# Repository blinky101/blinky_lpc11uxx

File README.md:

# LPC11uxx Example Project: Blinky

Simple Hello World-like blinky programs for the LPC11uxx platform.
This repositories contains three blinky programs, in increasing order of complexity / abstraction level:

1. [bare-metal](/bare-metal/): A blinky program in one file, with no dependencies at all
2. [basic](/basic/): Some of the low-level stuff is in separate functions, but still a very simple c program
3. [cpm](/cpm/): Using CPM as c package manager: reuseable dependencies are in separate repositories

See [the blinky website](https://blinky101.github.io/blinky_lpc11uxx/) and the per-project *README* files for more information.

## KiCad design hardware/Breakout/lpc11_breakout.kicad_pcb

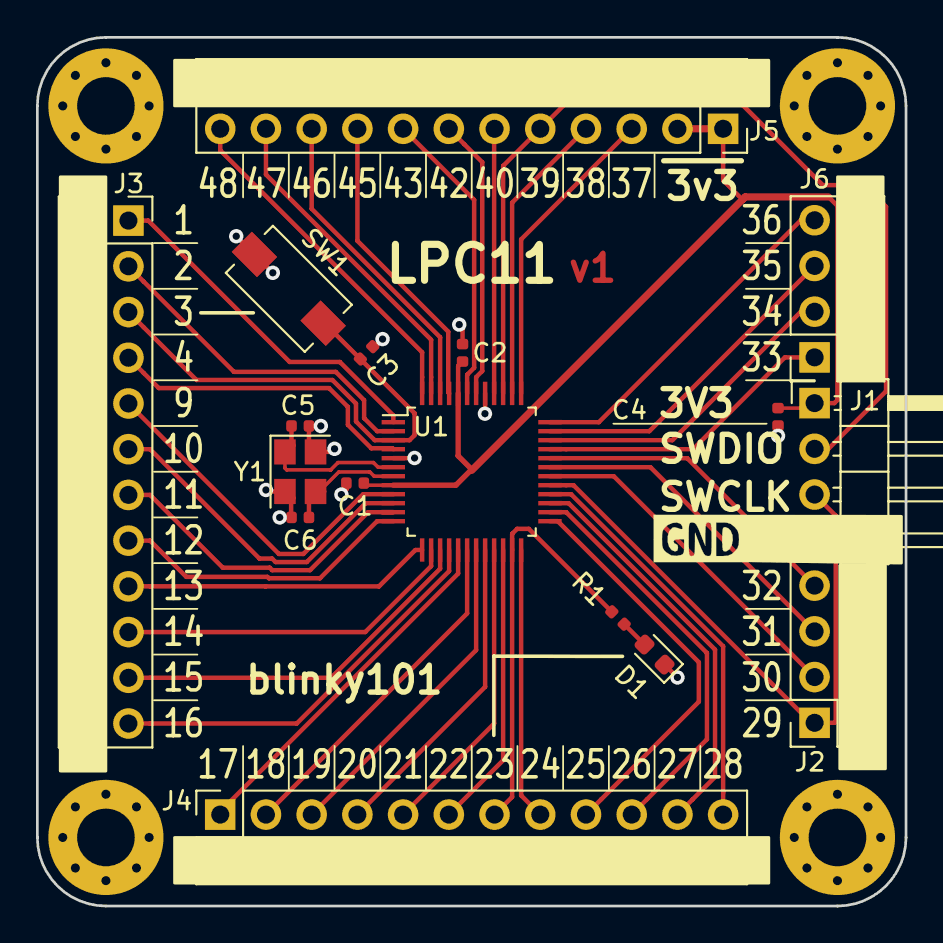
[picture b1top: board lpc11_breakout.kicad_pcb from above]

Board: 2 copper layers, 48.3 x 48.3 mm, 21 parts (0 on the bottom side), 47 nets.

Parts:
C1, C2, C4: 100nF; C_0402_1005Metric
C3, C5, C6: 18pF; C_0402_1005Metric
D1: LED; LED_0603_1608Metric
H1, H2, H3, H4: MountingHole_Pad; MountingHole_3.2mm_M3_Pad_Via
J1: Conn_01x04_Male; PinHeader_1x04_P2.54mm_Horizontal
J2, J6: Conn_02x04_Odd_Even; PinSocket_2x04_P2.54mm_Vertical
J3, J4, J5: Conn_02x12_Odd_Even; PinSocket_2x12_P2.54mm_Vertical
R1: 270R; R_0402_1005Metric
SW1: SW_Push; SW_SPST_EVQPE1
U1: LPC1115JBD48-303; LQFP-48_7x7mm_P0.5mm
Y1: MCSJK-7U-12.00-10-10-80-B-10; Crystal_SMD_3225-4Pin_3.2x2.5mm

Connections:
+3V3: C1.1, C2.1, C4.1, J1.1, J5.1, J5.3, U1.8, U1.44
/1: J3.1, U1.1
/2: J3.3, U1.2
/3: C3.1, J3.5, SW1.1, U1.3
/4: J3.7, U1.4
/9: J3.9, U1.9
/10: J3.11, U1.10
/11: J3.13, U1.11
/12: J3.15, U1.12
/13: J3.17, U1.13
/14: J3.19, U1.14
/15: J3.21, U1.15
/16: J3.23, U1.16
/17: J4.1, U1.17
/18: J4.3, U1.18
/19: J4.5, U1.19
/20: J4.7, U1.20
/21: J4.9, U1.21
/22: J4.11, U1.22
/23: J4.13, R1.1, U1.23
/24: J4.15, U1.24
/25: J4.17, U1.25
/26: J4.19, U1.26
/27: J4.21, U1.27
/28: J4.23, U1.28
/30: J2.3, U1.30
/31: J2.5, U1.31
/32: J2.7, U1.32
/33: J6.1, U1.33
/34: J6.3, U1.34
/35: J6.5, U1.35
/36: J6.7, U1.36
/37: J5.5, U1.37
/38: J5.7, U1.38
/40: J5.11, U1.40
/42: J5.13, U1.42
/43: J5.15, U1.43
/45: J5.17, U1.45
/46: J5.19, U1.46
/47: J5.21, U1.47
/48: J5.23, U1.48
/SWCLK_29: J1.3, J2.1, U1.29
/SWDIO_39: J1.2, J5.9, U1.39
GND: C1.2, C2.2, C3.2, C4.2, C5.2, C6.2, D1.1, J1.4, J2.2, J2.4, J2.6, J2.8, J3.2, J3.4, J3.6, J3.8, J3.10, J3.12, J3.14, J3.16, J3.18, J3.20, J3.22, J3.24, J4.2, J4.4, J4.6, J4.8, J4.10, J4.12, J4.14, J4.16, J4.18, J4.20, J4.22, J4.24, J5.2, J5.4, J5.6, J5.8, J5.10, J5.12, J5.14, J5.16, J5.18, J5.20, J5.22, J5.24, J6.2, J6.4, J6.6, J6.8, SW1.2, U1.5, U1.41, Y1.2, Y1.4
unnamed: C5.1, U1.6, Y1.1
unnamed: C6.1, U1.7, Y1.3
unnamed: D1.2, R1.2

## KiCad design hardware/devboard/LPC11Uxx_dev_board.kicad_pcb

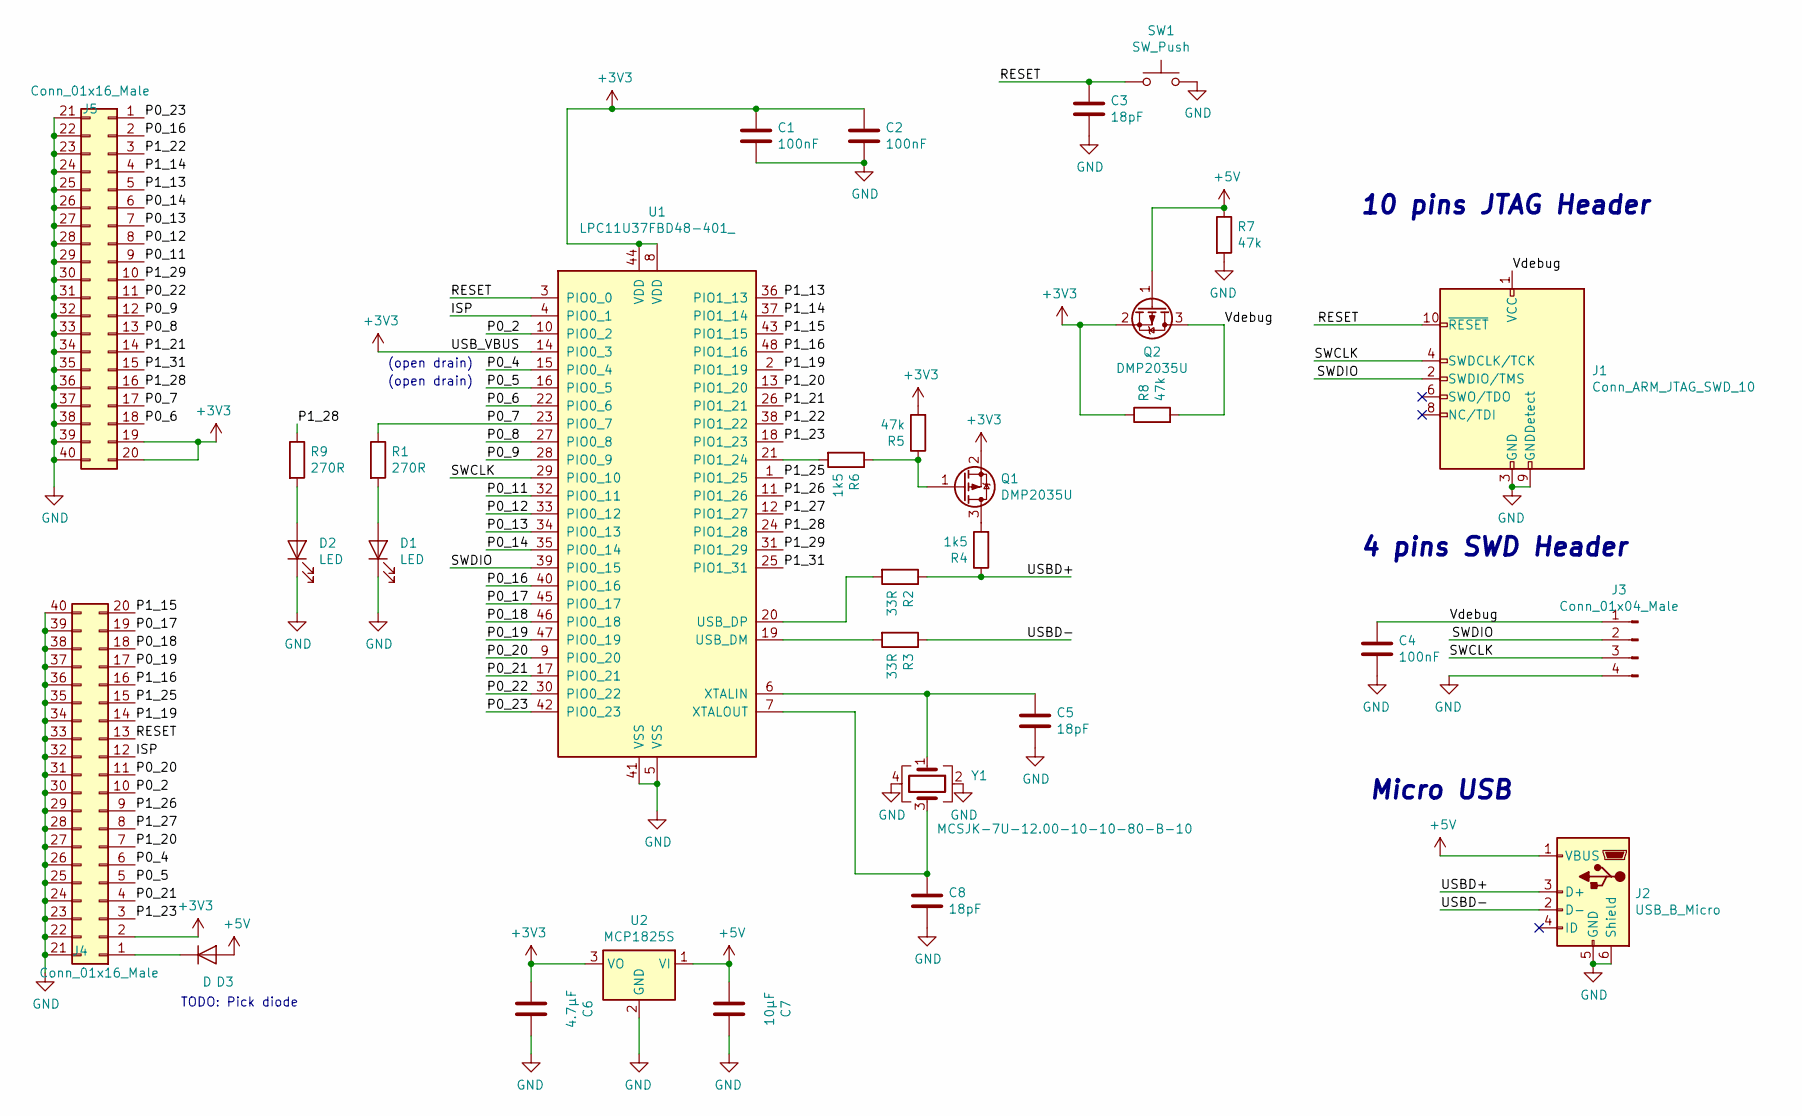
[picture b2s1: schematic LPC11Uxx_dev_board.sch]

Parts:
C1, C2, C4: 100nF; C_0402_1005Metric
C3, C5, C8: 18pF; C_0402_1005Metric
C6: 4.7µF; C_0805_2012Metric
C7: 10µF; C_0805_2012Metric
D1, D2: LED; LED_0603_1608Metric
D3: D; D_SOD-123F
J1: Conn_ARM_JTAG_SWD_10; PinHeader_2x05_P1.27mm_Vertical_SMD
J2: USB_B_Micro; USB_Micro-B_Molex_47346-0001
J3: Conn_01x04_Male; PinHeader_1x04_P2.54mm_Horizontal
J4, J5: Conn_01x16_Male; PinHeader_2x20_P2.54mm_Vertical_numbers_topbottom
Q1, Q2: DMP2035U; SOT-23
R1, R9: 270R; R_0402_1005Metric
R2, R3: 33R; R_0402_1005Metric
R4, R6: 1k5; R_0402_1005Metric
R5, R7, R8: 47k; R_0402_1005Metric
SW1: SW_Push; SW_SPST_EVQPE1
U1: LPC11U37FBD48-401_; LQFP-48_7x7mm_P0.5mm
U2: MCP1825S; SOT-223-3_TabPin2
Y1: MCSJK-7U-12.00-10-10-80-B-10; Crystal_SMD_3225-4Pin_3.2x2.5mm

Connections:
+3V3: C1.1, C2.1, C6.2, J4.2, J5.19, J5.20, Q1.2 (S), Q2.2 (S), R5.2, R8.1, U1.8 (VDD), U1.14 (PIO0_3), U1.44 (VDD), U2.3 (VO)
+5V: C7.2, D3.2 (A), J2.1 (VBUS), Q2.1 (G), R7.1, U2.1 (VI)
/ISP: J4.12, U1.4 (PIO0_1)
/P0_2: J4.10, U1.10 (PIO0_2)
/P0_4: J4.6, U1.15 (PIO0_4)
/P0_5: J4.5, U1.16 (PIO0_5)
/P0_6: J5.18, U1.22 (PIO0_6)
/P0_7: J5.17, R1.1, U1.23 (PIO0_7)
/P0_8: J5.13, U1.27 (PIO0_8)
/P0_9: J5.12, U1.28 (PIO0_9)
/P0_11: J5.9, U1.32 (PIO0_11)
/P0_12: J5.8, U1.33 (PIO0_12)
/P0_13: J5.7, U1.34 (PIO0_13)
/P0_14: J5.6, U1.35 (PIO0_14)
/P0_16: J5.2, U1.40 (PIO0_16)
/P0_17: J4.19, U1.45 (PIO0_17)
/P0_18: J4.18, U1.46 (PIO0_18)
/P0_19: J4.17, U1.47 (PIO0_19)
/P0_20: J4.11, U1.9 (PIO0_20)
/P0_21: J4.4, U1.17 (PIO0_21)
/P0_22: J5.11, U1.30 (PIO0_22)
/P0_23: J5.1, U1.42 (PIO0_23)
/P1_13: J5.5, U1.36 (PIO1_13)
/P1_14: J5.4, U1.37 (PIO1_14)
/P1_15: J4.20, U1.43 (PIO1_15)
/P1_16: J4.16, U1.48 (PIO1_16)
/P1_19: J4.14, U1.2 (PIO1_19)
/P1_20: J4.7, U1.13 (PIO1_20)
/P1_21: J5.14, U1.26 (PIO1_21)
/P1_22: J5.3, U1.38 (PIO1_22)
/P1_23: J4.3, U1.18 (PIO1_23)
/P1_25: J4.15, U1.1 (PIO1_25)
/P1_26: J4.9, U1.11 (PIO1_26)
/P1_27: J4.8, U1.12 (PIO1_27)
/P1_28: J5.16, R9.1, U1.24 (PIO1_28)
/P1_29: J5.10, U1.31 (PIO1_29)
/P1_31: J5.15, U1.25 (PIO1_31)
/RESET: C3.1, J1.10 (~RESET~), J4.13, SW1.1, U1.3 (PIO0_0)
/SWCLK: J1.4 (SWDCLK/TCK), J3.3, U1.29 (PIO0_10)
/SWDIO: J1.2 (SWDIO/TMS), J3.2, U1.39 (PIO0_15)
/USBD+: J2.3 (D+), R2.1, R4.1
/USBD-: J2.2 (D-), R3.1
/Vdebug: C4.1, J1.1 (VCC), J3.1, Q2.3 (D), R8.2
GND: C1.2, C2.2, C3.2, C4.2, C5.2, C6.1, C7.1, C8.2, D1.1 (K), D2.1 (K), J1.3 (GND), J1.5 (GND), J1.9 (GNDDetect), J2.5 (GND), J2.6 (Shield), J3.4, J4.21, J4.22, J4.23, J4.24, J4.25, J4.26, J4.27, J4.28, J4.29, J4.30, J4.31, J4.32, J4.33, J4.34, J4.35, J4.36, J4.37, J4.38, J4.39, J4.40, J5.21, J5.22, J5.23, J5.24, J5.25, J5.26, J5.27, J5.28, J5.29, J5.30, J5.31, J5.32, J5.33, J5.34, J5.35, J5.36, J5.37, J5.38, J5.39, J5.40, R7.2, SW1.2, U1.5 (VSS), U1.41 (VSS), U2.2 (GND), Y1.2, Y1.4
unnamed: C5.1, U1.6 (XTALIN), Y1.1
unnamed: C8.1, U1.7 (XTALOUT), Y1.3
unnamed: D1.2 (A), R1.2
unnamed: D2.2 (A), R9.2
unnamed: D3.1 (K), J4.1
unnamed: Q1.1 (G), R5.1, R6.1
unnamed: Q1.3 (D), R4.2
unnamed: R2.2, U1.20 (USB_DP)
unnamed: R3.2, U1.19 (USB_DM)
unnamed: R6.2, U1.21 (PIO1_24)

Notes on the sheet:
10 pins JTAG Header
4 pins SWD Header
Micro USB
(open drain)
TODO: Pick diode

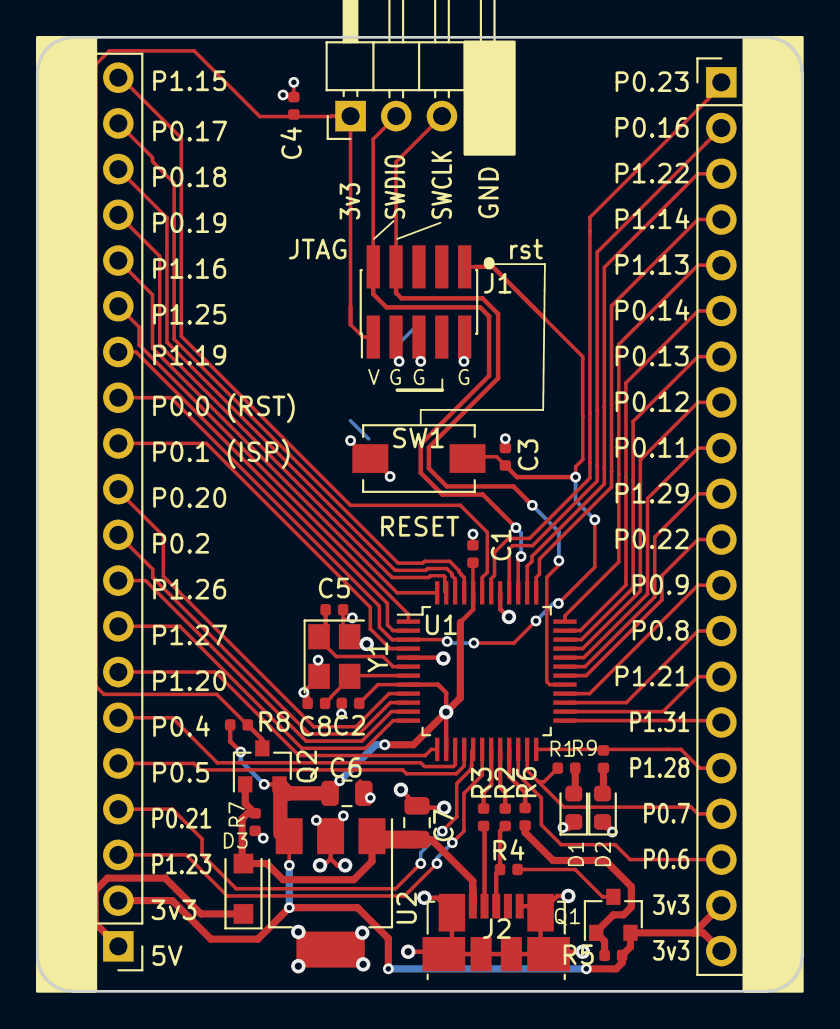
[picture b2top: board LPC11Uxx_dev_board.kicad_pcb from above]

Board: 2 copper layers, 42.5 x 53.0 mm, 31 parts (0 on the bottom side), 54 nets.

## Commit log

2018-08-27 first commit: a working blinky demo
2018-08-28 simplify example: use boardconfig as intended
2018-08-28 README: add CPM explanation
2018-08-28 rename dependencies: convention is now <purpose>_<chip>
2018-08-29 Add vscode launch file for debugging with black magic probe
2018-08-29 Add uart peripheral example.
    This can be used for printf debugging using the blackmagic probe or any
    other serial -> usb converter.
2018-08-30 Set theme jekyll-theme-minimal
2018-08-31 flash via mcu_debug package, which supports black magic probe
2018-08-31 Add standalone bare-metal blinky project with makefile
2018-08-31 move cpm project to subfolder
2018-08-31 Update cpm README
2018-08-31 docs: add image of lpcxpresso board
2018-08-31 Add 'basic' blinky project with startup code and chip headers
    This project shows a very simple 'chip library' and board support
    package.
2018-08-31 Add binary/elf file for bare-metal project
    Normally you don't want binary output files in the repository, but these
    are shipped to serve as a reference for people following the guide in
    /docs/
2018-08-31 bare-metal: fix 'make clean'
2018-09-03 bare-metal: add README
2018-09-03 bare-metal: simplify code by removing unused stuff
2018-09-03 bare-metal: simplify code + linker script
    all unused stuff is removed as much as possible
2018-09-03 project 'basic': add README
2018-09-03 project 'basic': fix target 'make clean'
2018-09-03 project 'cpm': remove some unused code
2018-09-03 bare-metal: gpio does not need pullup/pulldown
2018-09-03 docs: add images of lpcxpresso board
2018-09-03 Add tutorial_part1 file: wip
    First attempt to write about the blinky code. Still needs the linker
    file and isr steps.
2018-09-03 docs: add img
2018-09-03 update overview image
2018-09-03 Update linker file for lpc11u14 and add linker section to tutorial
2018-09-03 Update index.md
    some typos
2018-09-03 add link to first tutorial in index.md
2018-09-03 Set theme jekyll-theme-leap-day
2018-09-03 Support powering the board via Black Magic Probe debugger
    See config.cmake.example: the feature is off by default
2018-09-04 Move gettings started to separate page as part 0
2018-09-04 update tutorial part 1
2018-09-04 Update getting_started: add title in frontmatter
2018-09-04 trying to overwrite theme styling
2018-09-04 Add logos to theme
2018-09-04 Fix logo height in header
2018-09-04 Add light logo
2018-09-04 update headline
2018-09-04 Trying different logo
2018-09-04 try yellow logo
2018-09-05 Update tutorial_part3.md
    tutorial part3 is not finished yet, but this is a start...
2018-09-12 bare-metal README: add FAQ about bmp tpwr_enable feature
2018-09-12 cpm README: add required step: create config.cmake
2018-09-12 bare-metal: latest elf file
2018-09-12 update images
2018-09-14 website: add more explicit link to repository
2018-09-14 Update README.md
    remove obsolete reference to our 'custom board'
2018-09-24 Add Kicad design files for the Blinky board
    Made with Kicad V5
2018-10-04 Add frame with tooling holes and 4x LPC11 Blinkyboard.
2018-10-04 Add warnings about powering via JTAG connector
2018-10-04 cpm project: remove redundant code from CMakeLists
2018-10-17 Use crystal symbol from our library
2018-10-26 PCB layout: minor adjustments
2018-11-19 Update chip and startup library dependencies
    instead of lpc11uxx we can use the more general lpc11xxx libs
2018-11-20 Hardware: add BOM
2018-12-14 Fix launch.json
2019-03-06 Add new pcb: lpc11u37 dev board with complete header breakout
2019-03-06 Pick diode
2019-03-07 Create lpc11 breakout board
    Should be compatible with the entire LPC11 LQFP48 series
2019-03-07 Move old blinky board to blinky/ subdir
2019-03-08 Add framed pcbs for production
2019-03-08 Breakout PCB: Fix frame tooling hole-to-hole distance to multiple of 20mm
2019-03-08 Devboard PCB: Fix frame tooling hole-to-hole distance to multiple of 20mm
2019-03-21 Update some components for lpc11
2019-03-21 Fix bug on LPC11 breakout board: SWDIO pin
